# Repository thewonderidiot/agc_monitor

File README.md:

# AGC Monitor

This is a modern reimplementation of the AGC Monitor, for use with a real Apollo Guidance Computer. The panel layout and behavior were implemented according to pictures and descriptions from [E-2026, User's Guide to the AGC Monitor (Core Rope Simulator)](https://virtualagc.github.io/virtualagc/Documents/HSI-208487.pdf). Both the descriptions and pictures in this document leave a lot to be desired, so best guesses were made where concrete information was not available. All logic is implemented in a [Numato Lab Styx Z7 FPGA Module](https://numato.com/product/styx-zynq-7020-fpga-module), which is connected to the AGC via interface circuits powered by the AGC itself. Host interfacing is done via FTDI Synchronous FIFO. The host GUI is implemented in python using PySide2.

An early version of this project was shown in [episode 8 of the Apollo Guidance Computer Restoration video series](https://www.youtube.com/watch?v=ThOXgcOOA1M&list=PL-_93BVApb59FWrLZfdlisi_x7-Ut_-w7&index=11), and it played a central role for the rest of the restoration.

*Original AGC Monitor panel and modern GUI*

*Monitor board installed in an AGC for testing*

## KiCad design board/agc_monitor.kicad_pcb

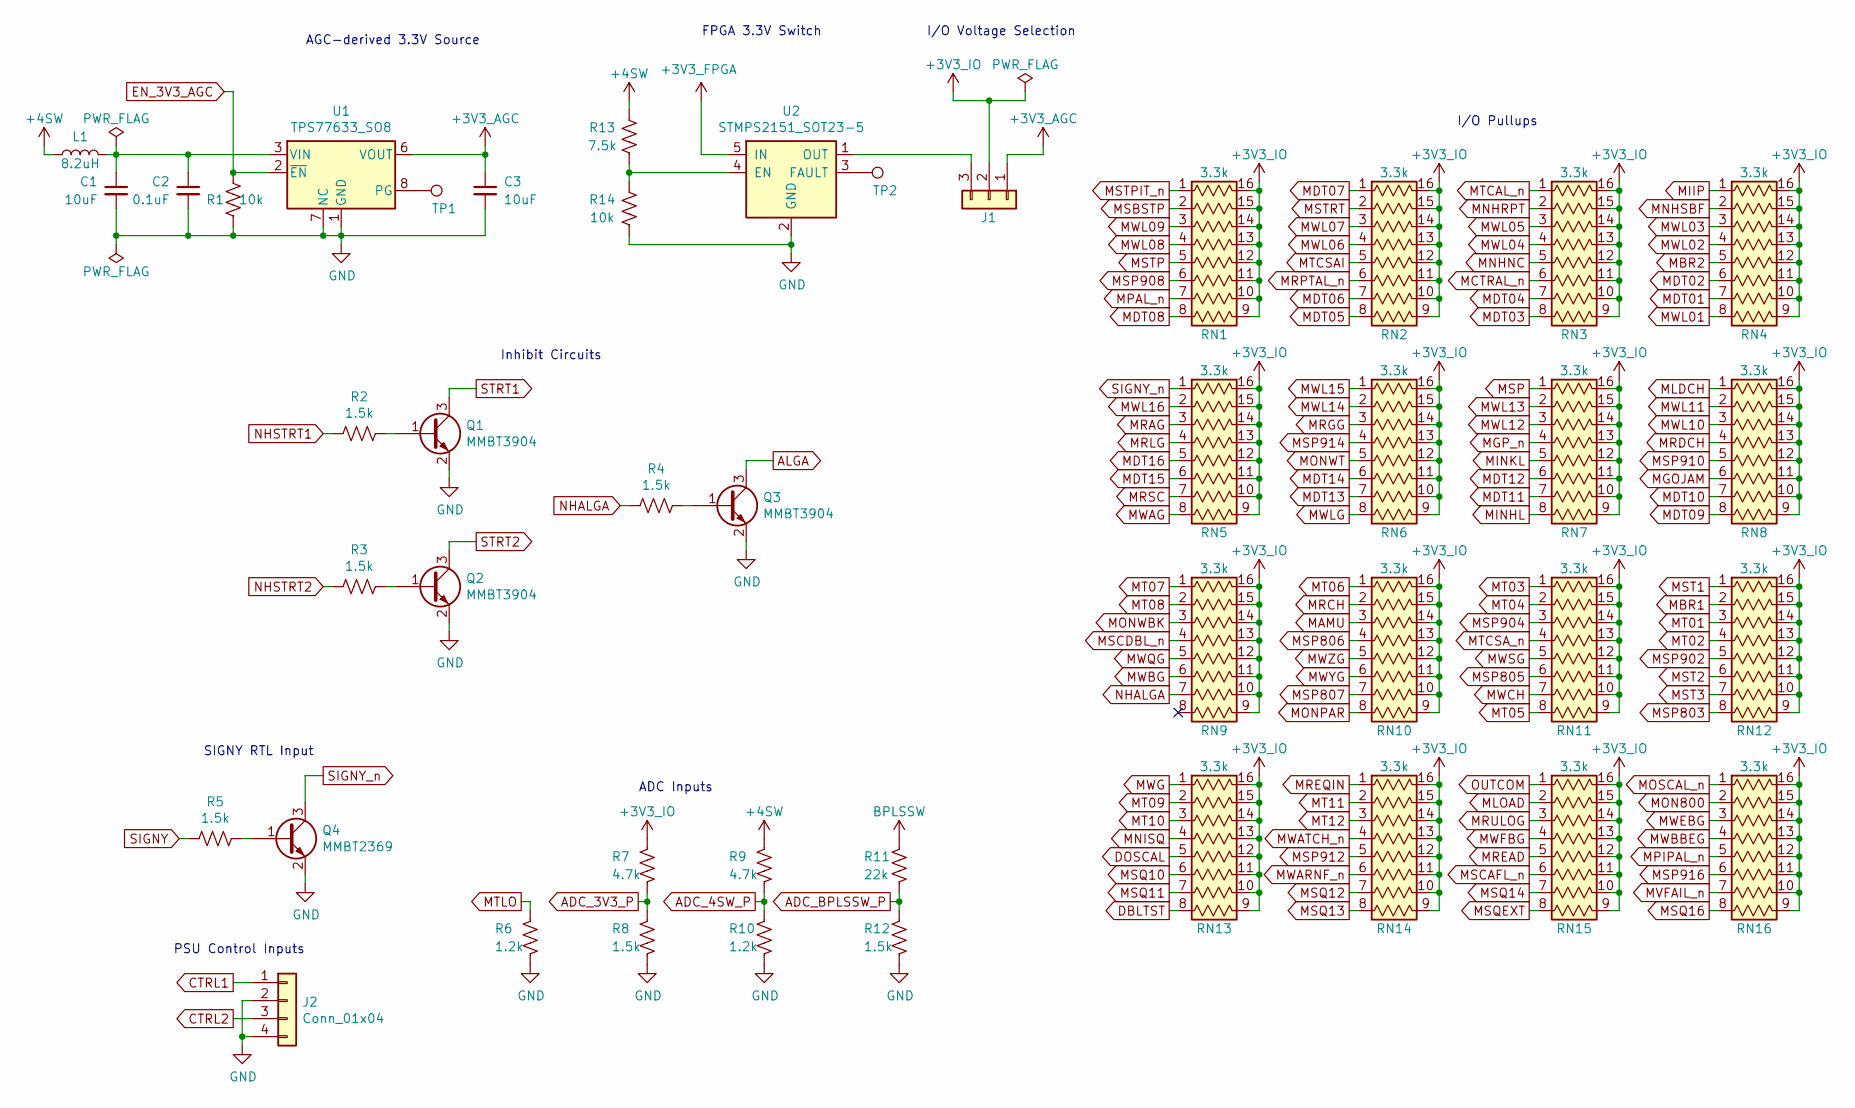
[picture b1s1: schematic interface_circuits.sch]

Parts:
C1, C3: 10uF; C_1206_3216Metric
C2: 0.1uF; C_0603_1608Metric
J1: Conn_01x03; PinHeader_1x03_P2.00mm_Vertical
J2: Conn_01x04; PinSocket_2x02_P2.54mm_Horizontal
L1: 8.2uH; L_1812_4532Metric
Q1, Q2, Q3: MMBT3904; SOT-23
Q4: MMBT2369; SOT-23
R1, R14: 10k; R_0603_1608Metric
R2, R3, R4, R5, R8, R12: 1.5k; R_0603_1608Metric
R6, R10: 1.2k; R_0603_1608Metric
R7, R9: 4.7k; R_0603_1608Metric
R11: 22k; R_0603_1608Metric
R13: 7.5k; R_0603_1608Metric
RN1, RN2, RN3, RN4, RN5, RN6, RN7, RN8, RN9, RN10, RN11, RN12, RN13, RN14, RN15, RN16: 3.3k; SOIC-16W_5.3x10.2mm_P1.27mm
TP1, TP2: TestPoint; TestPoint_Pad_D1.0mm
U1: TPS77633_SO8; SOIC-8_3.9x4.9mm_P1.27mm
U2: STMPS2151_SOT23-5; SOT-23-5

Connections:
+3V3_AGC: C3.1, J1.1, U1.5 (VOUT), U1.6 (VOUT)
+3V3_FPGA: U2.5 (IN); also elsewhere on the board
+3V3_IO: J1.2, R7.1, RN1.9 (R8B), RN1.10 (R7B), RN1.11 (R6B), RN1.12 (R5B), RN1.13 (R4B), RN1.14 (R3B), RN1.15 (R2B), RN1.16 (R1B), RN2.9 (R8B), RN2.10 (R7B), RN2.11 (R6B), RN2.12 (R5B), RN2.13 (R4B), RN2.14 (R3B), RN2.15 (R2B), RN2.16 (R1B), RN3.9 (R8B), RN3.10 (R7B), RN3.11 (R6B), RN3.12 (R5B), RN3.13 (R4B), RN3.14 (R3B), RN3.15 (R2B), RN3.16 (R1B), RN4.9 (R8B), RN4.10 (R7B), RN4.11 (R6B), RN4.12 (R5B), RN4.13 (R4B), RN4.14 (R3B), RN4.15 (R2B), RN4.16 (R1B), RN5.9 (R8B), RN5.10 (R7B), RN5.11 (R6B), RN5.12 (R5B), RN5.13 (R4B), RN5.14 (R3B), RN5.15 (R2B), RN5.16 (R1B), RN6.9 (R8B), RN6.10 (R7B), RN6.11 (R6B), RN6.12 (R5B), RN6.13 (R4B), RN6.14 (R3B), RN6.15 (R2B), RN6.16 (R1B), RN7.9 (R8B), RN7.10 (R7B), RN7.11 (R6B), RN7.12 (R5B), RN7.13 (R4B), RN7.14 (R3B), RN7.15 (R2B), RN7.16 (R1B), RN8.9 (R8B), RN8.10 (R7B), RN8.11 (R6B), RN8.12 (R5B), RN8.13 (R4B), RN8.14 (R3B), RN8.15 (R2B), RN8.16 (R1B), RN9.9 (R8B), RN9.10 (R7B), RN9.11 (R6B), RN9.12 (R5B), RN9.13 (R4B), RN9.14 (R3B), RN9.15 (R2B), RN9.16 (R1B), RN10.9 (R8B), RN10.10 (R7B), RN10.11 (R6B), RN10.12 (R5B), RN10.13 (R4B), RN10.14 (R3B), RN10.15 (R2B), RN10.16 (R1B), RN11.9 (R8B), RN11.10 (R7B), RN11.11 (R6B), RN11.12 (R5B), RN11.13 (R4B), RN11.14 (R3B), RN11.15 (R2B), RN11.16 (R1B), RN12.9 (R8B), RN12.10 (R7B), RN12.11 (R6B), RN12.12 (R5B), RN12.13 (R4B), RN12.14 (R3B), RN12.15 (R2B), RN12.16 (R1B), RN13.9 (R8B), RN13.10 (R7B), RN13.11 (R6B), RN13.12 (R5B), RN13.13 (R4B), RN13.14 (R3B), RN13.15 (R2B), RN13.16 (R1B), RN14.9 (R8B), RN14.10 (R7B), RN14.11 (R6B), RN14.12 (R5B), RN14.13 (R4B), RN14.14 (R3B), RN14.15 (R2B), RN14.16 (R1B), RN15.9 (R8B), RN15.10 (R7B), RN15.11 (R6B), RN15.12 (R5B), RN15.13 (R4B), RN15.14 (R3B), RN15.15 (R2B), RN15.16 (R1B), RN16.9 (R8B), RN16.10 (R7B), RN16.11 (R6B), RN16.12 (R5B), RN16.13 (R4B), RN16.14 (R3B), RN16.15 (R2B), RN16.16 (R1B); also elsewhere on the board
+4SW: L1.1, R9.1, R13.1; also elsewhere on the board
ADC_3V3_P: R7.2, R8.1; also elsewhere on the board
ADC_4SW_P: R9.2, R10.1; also elsewhere on the board
ADC_BPLSSW_P: R11.2, R12.1; also elsewhere on the board
ALGA: Q3.3 (C); also elsewhere on the board
BPLSSW: R11.1; also elsewhere on the board
CTRL1: J2.1; also elsewhere on the board
CTRL2: J2.3; also elsewhere on the board
DBLTST: RN13.8 (R8A); also elsewhere on the board
DOSCAL: RN13.5 (R5A); also elsewhere on the board
EN_3V3_AGC: R1.1, U1.2 (~EN~); also elsewhere on the board
GND: C1.2, C2.2, C3.2, J2.2, J2.4, Q1.2 (E), Q2.2 (E), Q3.2 (E), Q4.2 (E), R1.2, R6.2, R8.2, R10.2, R12.2, R14.2, U1.1 (GND), U1.7 (NC), U2.2 (GND); also elsewhere on the board
MAMU: RN10.3 (R3A); also elsewhere on the board
MBR1: RN12.2 (R2A); also elsewhere on the board
MBR2: RN4.5 (R5A); also elsewhere on the board
MCTRAL_n: RN3.6 (R6A); also elsewhere on the board
MDT01: RN4.7 (R7A); also elsewhere on the board
MDT02: RN4.6 (R6A); also elsewhere on the board
MDT03: RN3.8 (R8A); also elsewhere on the board
MDT04: RN3.7 (R7A); also elsewhere on the board
MDT05: RN2.8 (R8A); also elsewhere on the board
MDT06: RN2.7 (R7A); also elsewhere on the board
MDT07: RN2.1 (R1A); also elsewhere on the board
MDT08: RN1.8 (R8A); also elsewhere on the board
MDT09: RN8.8 (R8A); also elsewhere on the board
MDT10: RN8.7 (R7A); also elsewhere on the board
MDT11: RN7.7 (R7A); also elsewhere on the board
MDT12: RN7.6 (R6A); also elsewhere on the board
MDT13: RN6.7 (R7A); also elsewhere on the board
MDT14: RN6.6 (R6A); also elsewhere on the board
MDT15: RN5.6 (R6A); also elsewhere on the board
MDT16: RN5.5 (R5A); also elsewhere on the board
MGOJAM: RN8.6 (R6A); also elsewhere on the board
MGP_n: RN7.4 (R4A); also elsewhere on the board
MIIP: RN4.1 (R1A); also elsewhere on the board
MINHL: RN7.8 (R8A); also elsewhere on the board
MINKL: RN7.5 (R5A); also elsewhere on the board
MLDCH: RN8.1 (R1A); also elsewhere on the board
MLOAD: RN15.2 (R2A); also elsewhere on the board
MNHNC: RN3.5 (R5A); also elsewhere on the board
MNHRPT: RN3.2 (R2A); also elsewhere on the board
MNHSBF: RN4.2 (R2A); also elsewhere on the board
MNISQ: RN13.4 (R4A); also elsewhere on the board
MON800: RN16.2 (R2A); also elsewhere on the board
MONPAR: RN10.8 (R8A); also elsewhere on the board
MONWBK: RN9.3 (R3A); also elsewhere on the board
MONWT: RN6.5 (R5A); also elsewhere on the board
MOSCAL_n: RN16.1 (R1A); also elsewhere on the board
MPAL_n: RN1.7 (R7A); also elsewhere on the board
MPIPAL_n: RN16.5 (R5A); also elsewhere on the board
MRAG: RN5.3 (R3A); also elsewhere on the board
MRCH: RN10.2 (R2A); also elsewhere on the board
MRDCH: RN8.4 (R4A); also elsewhere on the board
MREAD: RN15.5 (R5A); also elsewhere on the board
MREQIN: RN14.1 (R1A); also elsewhere on the board
MRGG: RN6.3 (R3A); also elsewhere on the board
MRLG: RN5.4 (R4A); also elsewhere on the board
MRPTAL_n: RN2.6 (R6A); also elsewhere on the board
MRSC: RN5.7 (R7A); also elsewhere on the board
MRULOG: RN15.3 (R3A); also elsewhere on the board
MSBSTP: RN1.2 (R2A); also elsewhere on the board
MSCAFL_n: RN15.6 (R6A); also elsewhere on the board
MSCDBL_n: RN9.4 (R4A); also elsewhere on the board
MSP: RN7.1 (R1A); also elsewhere on the board
MSP803: RN12.8 (R8A); also elsewhere on the board
MSP805: RN11.6 (R6A); also elsewhere on the board
MSP806: RN10.4 (R4A); also elsewhere on the board
MSP807: RN10.7 (R7A); also elsewhere on the board
MSP902: RN12.5 (R5A); also elsewhere on the board
MSP904: RN11.3 (R3A); also elsewhere on the board
MSP908: RN1.6 (R6A); also elsewhere on the board
MSP910: RN8.5 (R5A); also elsewhere on the board
MSP912: RN14.5 (R5A); also elsewhere on the board
MSP914: RN6.4 (R4A); also elsewhere on the board
MSP916: RN16.6 (R6A); also elsewhere on the board
MSQ10: RN13.6 (R6A); also elsewhere on the board
MSQ11: RN13.7 (R7A); also elsewhere on the board
MSQ12: RN14.7 (R7A); also elsewhere on the board
MSQ13: RN14.8 (R8A); also elsewhere on the board
MSQ14: RN15.7 (R7A); also elsewhere on the board
MSQ16: RN16.8 (R8A); also elsewhere on the board
MSQEXT: RN15.8 (R8A); also elsewhere on the board
MST1: RN12.1 (R1A); also elsewhere on the board
MST2: RN12.6 (R6A); also elsewhere on the board
MST3: RN12.7 (R7A); also elsewhere on the board
MSTP: RN1.5 (R5A); also elsewhere on the board
MSTPIT_n: RN1.1 (R1A); also elsewhere on the board
MSTRT: RN2.2 (R2A); also elsewhere on the board
MT01: RN12.3 (R3A); also elsewhere on the board
MT02: RN12.4 (R4A); also elsewhere on the board
MT03: RN11.1 (R1A); also elsewhere on the board
MT04: RN11.2 (R2A); also elsewhere on the board
MT05: RN11.8 (R8A); also elsewhere on the board
MT06: RN10.1 (R1A); also elsewhere on the board
MT07: RN9.1 (R1A); also elsewhere on the board
MT08: RN9.2 (R2A); also elsewhere on the board
MT09: RN13.2 (R2A); also elsewhere on the board
MT10: RN13.3 (R3A); also elsewhere on the board
MT11: RN14.2 (R2A); also elsewhere on the board
MT12: RN14.3 (R3A); also elsewhere on the board
MTCAL_n: RN3.1 (R1A); also elsewhere on the board
MTCSAI: RN2.5 (R5A); also elsewhere on the board
MTCSA_n: RN11.4 (R4A); also elsewhere on the board
MTLO: R6.1; also elsewhere on the board
MVFAIL_n: RN16.7 (R7A); also elsewhere on the board
MWAG: RN5.8 (R8A); also elsewhere on the board
MWARNF_n: RN14.6 (R6A); also elsewhere on the board
MWATCH_n: RN14.4 (R4A); also elsewhere on the board
MWBBEG: RN16.4 (R4A); also elsewhere on the board
MWBG: RN9.6 (R6A); also elsewhere on the board
MWCH: RN11.7 (R7A); also elsewhere on the board
MWEBG: RN16.3 (R3A); also elsewhere on the board
MWFBG: RN15.4 (R4A); also elsewhere on the board
MWG: RN13.1 (R1A); also elsewhere on the board
MWL01: RN4.8 (R8A); also elsewhere on the board
MWL02: RN4.4 (R4A); also elsewhere on the board
MWL03: RN4.3 (R3A); also elsewhere on the board
MWL04: RN3.4 (R4A); also elsewhere on the board
MWL05: RN3.3 (R3A); also elsewhere on the board
MWL06: RN2.4 (R4A); also elsewhere on the board
MWL07: RN2.3 (R3A); also elsewhere on the board
MWL08: RN1.4 (R4A); also elsewhere on the board
MWL09: RN1.3 (R3A); also elsewhere on the board
MWL10: RN8.3 (R3A); also elsewhere on the board
MWL11: RN8.2 (R2A); also elsewhere on the board
MWL12: RN7.3 (R3A); also elsewhere on the board
MWL13: RN7.2 (R2A); also elsewhere on the board
MWL14: RN6.2 (R2A); also elsewhere on the board
MWL15: RN6.1 (R1A); also elsewhere on the board
MWL16: RN5.2 (R2A); also elsewhere on the board
MWLG: RN6.8 (R8A); also elsewhere on the board
MWQG: RN9.5 (R5A); also elsewhere on the board
MWSG: RN11.5 (R5A); also elsewhere on the board
MWYG: RN10.6 (R6A); also elsewhere on the board
MWZG: RN10.5 (R5A); also elsewhere on the board
NHALGA: R4.2, RN9.7 (R7A); also elsewhere on the board
NHSTRT1: R2.2; also elsewhere on the board
NHSTRT2: R3.2; also elsewhere on the board
unnamed: C1.1, C2.1, L1.2, U1.3 (VIN), U1.4 (VIN)
unnamed: J1.3, U2.1 (OUT)
unnamed: Q1.1 (B), R2.1
unnamed: Q2.1 (B), R3.1
unnamed: Q3.1 (B), R4.1
unnamed: Q4.1 (B), R5.1
unnamed: R13.2, R14.1, U2.4 (EN)
unnamed: TP1.1, U1.8 (PG)
unnamed: TP2.1, U2.3 (FAULT)
OUTCOM: RN15.1 (R1A); also elsewhere on the board
SIGNY: R5.2; also elsewhere on the board
SIGNY_n: Q4.3 (C), RN5.1 (R1A); also elsewhere on the board
STRT1: Q1.3 (C); also elsewhere on the board
STRT2: Q2.3 (C); also elsewhere on the board

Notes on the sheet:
AGC-derived 3.3V Source
I/O Voltage Selection
ADC Inputs
I/O Pullups
Inhibit Circuits
PSU Control Inputs
SIGNY RTL Input
FPGA 3.3V Switch

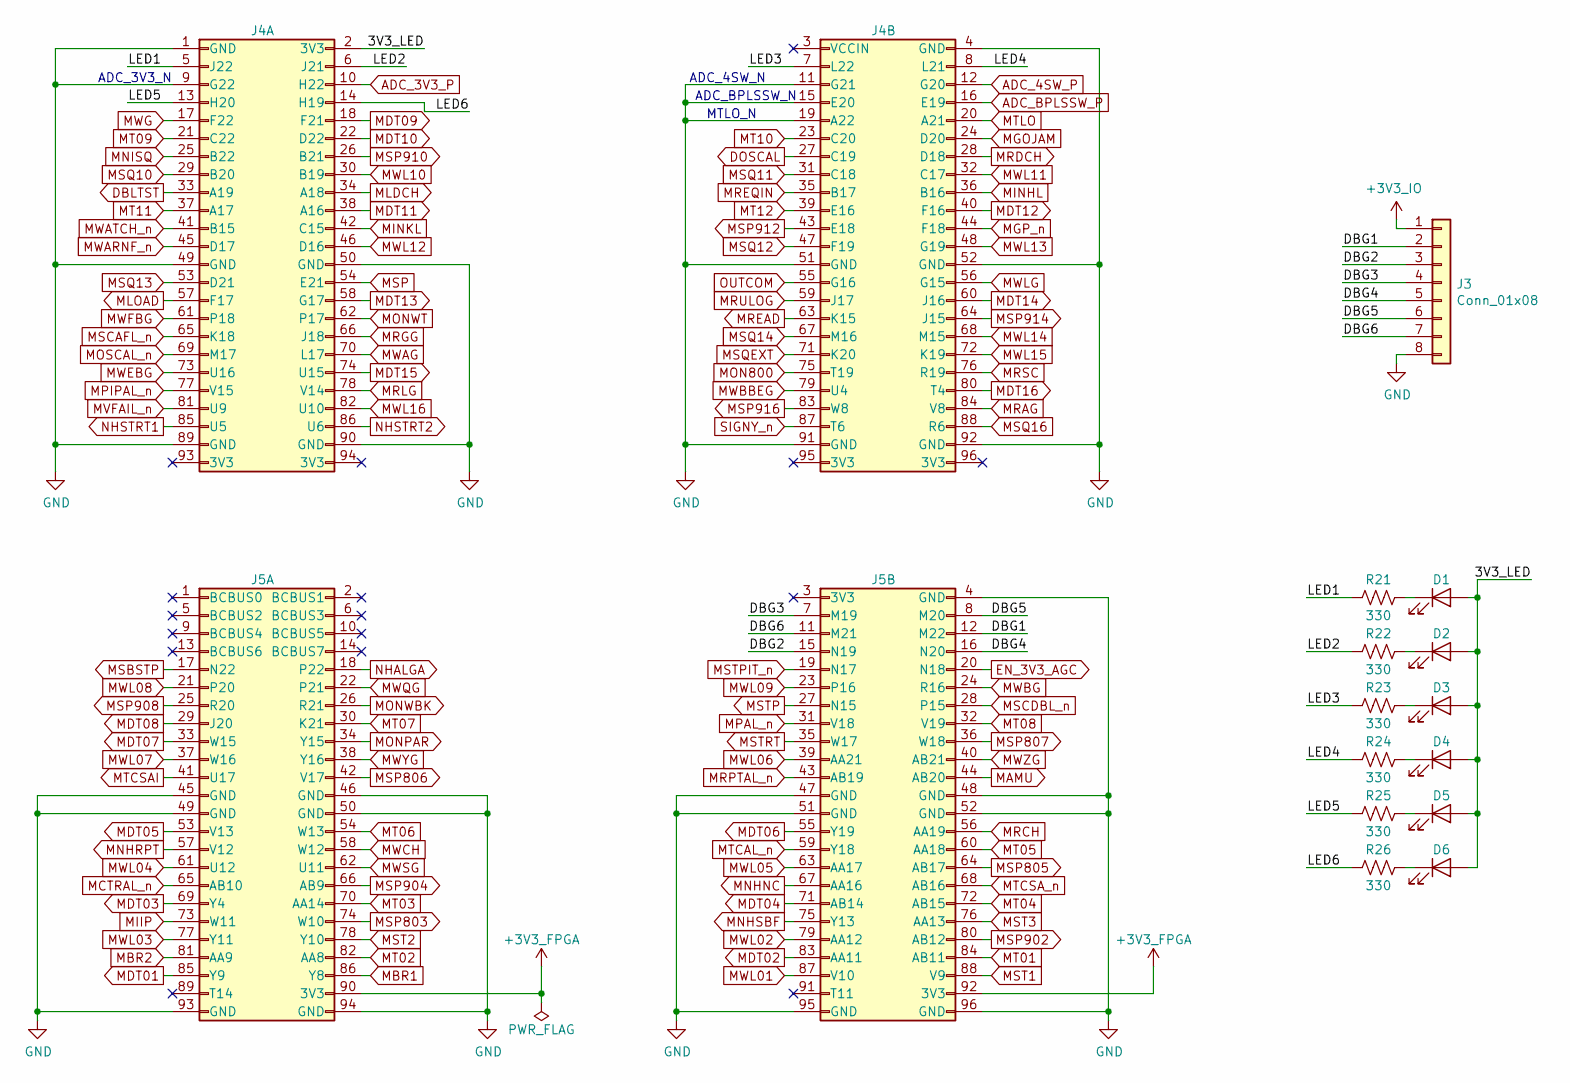
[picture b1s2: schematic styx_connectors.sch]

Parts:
D1, D2, D3, D4, D5, D6: LED; LED_0603_1608Metric
J3: Conn_01x08; PinSocket_2x04_P2.54mm_Horizontal
J4: Styx_P4; PinHeader_4x24_P2.54mm_Vertical
J5: Styx_P5; PinHeader_4x24_P2.54mm_Vertical
R21, R22, R23, R24, R25, R26: 330; R_0603_1608Metric

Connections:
+3V3_FPGA: J5.90 (3V3), J5.92 (3V3); also elsewhere on the board
+3V3_IO: J3.1; also elsewhere on the board
/StyxConnectors/3V3_LED: D1.2 (A), D2.2 (A), D3.2 (A), D4.2 (A), D5.2 (A), D6.2 (A), J4.2 (3V3)
/StyxConnectors/DBG1: J3.2, J5.12 (M22)
/StyxConnectors/DBG2: J3.3, J5.15 (N19)
/StyxConnectors/DBG3: J3.4, J5.7 (M19)
/StyxConnectors/DBG4: J3.5, J5.16 (N20)
/StyxConnectors/DBG5: J3.6, J5.8 (M20)
/StyxConnectors/DBG6: J3.7, J5.11 (M21)
/StyxConnectors/LED1: J4.5 (J22), R21.2
/StyxConnectors/LED2: J4.6 (J21), R22.2
/StyxConnectors/LED3: J4.7 (L22), R23.2
/StyxConnectors/LED4: J4.8 (L21), R24.2
/StyxConnectors/LED5: J4.13 (H20), R25.2
/StyxConnectors/LED6: J4.14 (H19), R26.2
ADC_3V3_P: J4.10 (H22); also elsewhere on the board
ADC_4SW_P: J4.12 (G20); also elsewhere on the board
ADC_BPLSSW_P: J4.16 (E19); also elsewhere on the board
DBLTST: J4.33 (A19); also elsewhere on the board
DOSCAL: J4.27 (C19); also elsewhere on the board
EN_3V3_AGC: J5.20 (N18); also elsewhere on the board
GND: J3.8, J4.1 (GND), J4.4 (GND), J4.9 (G22), J4.11 (G21), J4.15 (E20), J4.19 (A22), J4.49 (GND), J4.50 (GND), J4.51 (GND), J4.52 (GND), J4.89 (GND), J4.90 (GND), J4.91 (GND), J4.92 (GND), J5.4 (GND), J5.45 (GND), J5.46 (GND), J5.47 (GND), J5.48 (GND), J5.49 (GND), J5.50 (GND), J5.51 (GND), J5.52 (GND), J5.93 (GND), J5.94 (GND), J5.95 (GND), J5.96 (GND); also elsewhere on the board
MAMU: J5.44 (AB20); also elsewhere on the board
MBR1: J5.86 (Y8); also elsewhere on the board
MBR2: J5.81 (AA9); also elsewhere on the board
MCTRAL_n: J5.65 (AB10); also elsewhere on the board
MDT01: J5.85 (Y9); also elsewhere on the board
MDT02: J5.83 (AA11); also elsewhere on the board
MDT03: J5.69 (Y4); also elsewhere on the board
MDT04: J5.71 (AB14); also elsewhere on the board
MDT05: J5.53 (V13); also elsewhere on the board
MDT06: J5.55 (Y19); also elsewhere on the board
MDT07: J5.33 (W15); also elsewhere on the board
MDT08: J5.29 (J20); also elsewhere on the board
MDT09: J4.18 (F21); also elsewhere on the board
MDT10: J4.22 (D22); also elsewhere on the board
MDT11: J4.38 (A16); also elsewhere on the board
MDT12: J4.40 (F16); also elsewhere on the board
MDT13: J4.58 (G17); also elsewhere on the board
MDT14: J4.60 (J16); also elsewhere on the board
MDT15: J4.74 (U15); also elsewhere on the board
MDT16: J4.80 (T4); also elsewhere on the board
MGOJAM: J4.24 (D20); also elsewhere on the board
MGP_n: J4.44 (F18); also elsewhere on the board
MIIP: J5.73 (W11); also elsewhere on the board
MINHL: J4.36 (B16); also elsewhere on the board
MINKL: J4.42 (C15); also elsewhere on the board
MLDCH: J4.34 (A18); also elsewhere on the board
MLOAD: J4.57 (F17); also elsewhere on the board
MNHNC: J5.67 (AA16); also elsewhere on the board
MNHRPT: J5.57 (V12); also elsewhere on the board
MNHSBF: J5.75 (Y13); also elsewhere on the board
MNISQ: J4.25 (B22); also elsewhere on the board
MON800: J4.75 (T19); also elsewhere on the board
MONPAR: J5.34 (Y15); also elsewhere on the board
MONWBK: J5.26 (R21); also elsewhere on the board
MONWT: J4.62 (P17); also elsewhere on the board
MOSCAL_n: J4.69 (M17); also elsewhere on the board
MPAL_n: J5.31 (V18); also elsewhere on the board
MPIPAL_n: J4.77 (V15); also elsewhere on the board
MRAG: J4.84 (V8); also elsewhere on the board
MRCH: J5.56 (AA19); also elsewhere on the board
MRDCH: J4.28 (D18); also elsewhere on the board
MREAD: J4.63 (K15); also elsewhere on the board
MREQIN: J4.35 (B17); also elsewhere on the board
MRGG: J4.66 (J18); also elsewhere on the board
MRLG: J4.78 (V14); also elsewhere on the board
MRPTAL_n: J5.43 (AB19); also elsewhere on the board
MRSC: J4.76 (R19); also elsewhere on the board
MRULOG: J4.59 (J17); also elsewhere on the board
MSBSTP: J5.17 (N22); also elsewhere on the board
MSCAFL_n: J4.65 (K18); also elsewhere on the board
MSCDBL_n: J5.28 (P15); also elsewhere on the board
MSP: J4.54 (E21); also elsewhere on the board
MSP803: J5.74 (W10); also elsewhere on the board
MSP805: J5.64 (AB17); also elsewhere on the board
MSP806: J5.42 (V17); also elsewhere on the board
MSP807: J5.36 (W18); also elsewhere on the board
MSP902: J5.80 (AB12); also elsewhere on the board
MSP904: J5.66 (AB9); also elsewhere on the board
MSP908: J5.25 (R20); also elsewhere on the board
MSP910: J4.26 (B21); also elsewhere on the board
MSP912: J4.43 (E18); also elsewhere on the board
MSP914: J4.64 (J15); also elsewhere on the board
MSP916: J4.83 (W8); also elsewhere on the board
MSQ10: J4.29 (B20); also elsewhere on the board
MSQ11: J4.31 (C18); also elsewhere on the board
MSQ12: J4.47 (F19); also elsewhere on the board
MSQ13: J4.53 (D21); also elsewhere on the board
MSQ14: J4.67 (M16); also elsewhere on the board
MSQ16: J4.88 (R6); also elsewhere on the board
MSQEXT: J4.71 (K20); also elsewhere on the board
MST1: J5.88 (V9); also elsewhere on the board
MST2: J5.78 (Y10); also elsewhere on the board
MST3: J5.76 (AA13); also elsewhere on the board
MSTP: J5.27 (N15); also elsewhere on the board
MSTPIT_n: J5.19 (N17); also elsewhere on the board
MSTRT: J5.35 (W17); also elsewhere on the board
MT01: J5.84 (AB11); also elsewhere on the board
MT02: J5.82 (AA8); also elsewhere on the board
MT03: J5.70 (AA14); also elsewhere on the board
MT04: J5.72 (AB15); also elsewhere on the board
MT05: J5.60 (AA18); also elsewhere on the board
MT06: J5.54 (W13); also elsewhere on the board
MT07: J5.30 (K21); also elsewhere on the board
MT08: J5.32 (V19); also elsewhere on the board
MT09: J4.21 (C22); also elsewhere on the board
MT10: J4.23 (C20); also elsewhere on the board
MT11: J4.37 (A17); also elsewhere on the board
MT12: J4.39 (E16); also elsewhere on the board
MTCAL_n: J5.59 (Y18); also elsewhere on the board
MTCSAI: J5.41 (U17); also elsewhere on the board
MTCSA_n: J5.68 (AB16); also elsewhere on the board
MTLO: J4.20 (A21); also elsewhere on the board
MVFAIL_n: J4.81 (U9); also elsewhere on the board
MWAG: J4.70 (L17); also elsewhere on the board
MWARNF_n: J4.45 (D17); also elsewhere on the board
MWATCH_n: J4.41 (B15); also elsewhere on the board
MWBBEG: J4.79 (U4); also elsewhere on the board
MWBG: J5.24 (R16); also elsewhere on the board
MWCH: J5.58 (W12); also elsewhere on the board
MWEBG: J4.73 (U16); also elsewhere on the board
MWFBG: J4.61 (P18); also elsewhere on the board
MWG: J4.17 (F22); also elsewhere on the board
MWL01: J5.87 (V10); also elsewhere on the board
MWL02: J5.79 (AA12); also elsewhere on the board
MWL03: J5.77 (Y11); also elsewhere on the board
MWL04: J5.61 (U12); also elsewhere on the board
MWL05: J5.63 (AA17); also elsewhere on the board
MWL06: J5.39 (AA21); also elsewhere on the board
MWL07: J5.37 (W16); also elsewhere on the board
MWL08: J5.21 (P20); also elsewhere on the board
MWL09: J5.23 (P16); also elsewhere on the board
MWL10: J4.30 (B19); also elsewhere on the board
MWL11: J4.32 (C17); also elsewhere on the board
MWL12: J4.46 (D16); also elsewhere on the board
MWL13: J4.48 (G19); also elsewhere on the board
MWL14: J4.68 (M15); also elsewhere on the board
MWL15: J4.72 (K19); also elsewhere on the board
MWL16: J4.82 (U10); also elsewhere on the board
MWLG: J4.56 (G15); also elsewhere on the board
MWQG: J5.22 (P21); also elsewhere on the board
MWSG: J5.62 (U11); also elsewhere on the board
MWYG: J5.38 (Y16); also elsewhere on the board
MWZG: J5.40 (AB21); also elsewhere on the board
NHALGA: J5.18 (P22); also elsewhere on the board
NHSTRT1: J4.85 (U5); also elsewhere on the board
NHSTRT2: J4.86 (U6); also elsewhere on the board
unnamed: D1.1 (K), R21.1
unnamed: D2.1 (K), R22.1
unnamed: D3.1 (K), R23.1
unnamed: D4.1 (K), R24.1
unnamed: D5.1 (K), R25.1
unnamed: D6.1 (K), R26.1
OUTCOM: J4.55 (G16); also elsewhere on the board
SIGNY_n: J4.87 (T6); also elsewhere on the board

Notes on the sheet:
ADC_BPLSSW_N
ADC_4SW_N
MTLO_N
ADC_3V3_N

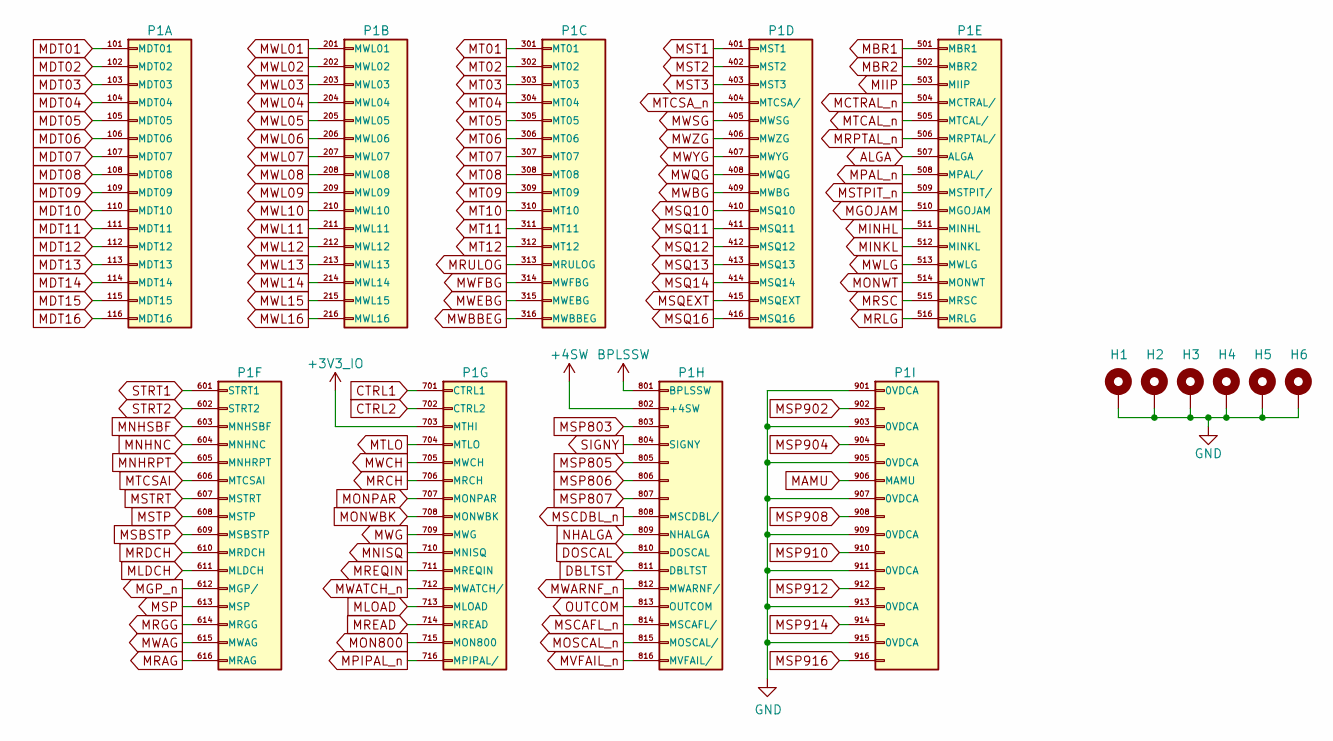
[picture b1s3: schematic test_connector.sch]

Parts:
H1, H2, H3, H4, H5, H6: MountingHole_Pad; MountingHole_ANSI_4
P1: test_connector

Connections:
+3V3_IO: P1.703 (MTHI); also elsewhere on the board
+4SW: P1.802 (+4SW); also elsewhere on the board
ALGA: P1.507 (ALGA); also elsewhere on the board
BPLSSW: P1.801 (BPLSSW); also elsewhere on the board
CTRL1: P1.701 (CTRL1); also elsewhere on the board
CTRL2: P1.702 (CTRL2); also elsewhere on the board
DBLTST: P1.811 (DBLTST); also elsewhere on the board
DOSCAL: P1.810 (DOSCAL); also elsewhere on the board
GND: H1.1, H2.1, H3.1, H4.1, H5.1, H6.1, P1.901 (0VDCA), P1.903 (0VDCA), P1.905 (0VDCA), P1.907 (0VDCA), P1.909 (0VDCA), P1.911 (0VDCA), P1.913 (0VDCA), P1.915 (0VDCA); also elsewhere on the board
MAMU: P1.906 (MAMU); also elsewhere on the board
MBR1: P1.501 (MBR1); also elsewhere on the board
MBR2: P1.502 (MBR2); also elsewhere on the board
MCTRAL_n: P1.504 (MCTRAL/); also elsewhere on the board
MDT01: P1.101 (MDT01); also elsewhere on the board
MDT02: P1.102 (MDT02); also elsewhere on the board
MDT03: P1.103 (MDT03); also elsewhere on the board
MDT04: P1.104 (MDT04); also elsewhere on the board
MDT05: P1.105 (MDT05); also elsewhere on the board
MDT06: P1.106 (MDT06); also elsewhere on the board
MDT07: P1.107 (MDT07); also elsewhere on the board
MDT08: P1.108 (MDT08); also elsewhere on the board
MDT09: P1.109 (MDT09); also elsewhere on the board
MDT10: P1.110 (MDT10); also elsewhere on the board
MDT11: P1.111 (MDT11); also elsewhere on the board
MDT12: P1.112 (MDT12); also elsewhere on the board
MDT13: P1.113 (MDT13); also elsewhere on the board
MDT14: P1.114 (MDT14); also elsewhere on the board
MDT15: P1.115 (MDT15); also elsewhere on the board
MDT16: P1.116 (MDT16); also elsewhere on the board
MGOJAM: P1.510 (MGOJAM); also elsewhere on the board
MGP_n: P1.612 (MGP/); also elsewhere on the board
MIIP: P1.503 (MIIP); also elsewhere on the board
MINHL: P1.511 (MINHL); also elsewhere on the board
MINKL: P1.512 (MINKL); also elsewhere on the board
MLDCH: P1.611 (MLDCH); also elsewhere on the board
MLOAD: P1.713 (MLOAD); also elsewhere on the board
MNHNC: P1.604 (MNHNC); also elsewhere on the board
MNHRPT: P1.605 (MNHRPT); also elsewhere on the board
MNHSBF: P1.603 (MNHSBF); also elsewhere on the board
MNISQ: P1.710 (MNISQ); also elsewhere on the board
MON800: P1.715 (MON800); also elsewhere on the board
MONPAR: P1.707 (MONPAR); also elsewhere on the board
MONWBK: P1.708 (MONWBK); also elsewhere on the board
MONWT: P1.514 (MONWT); also elsewhere on the board
MOSCAL_n: P1.815 (MOSCAL/); also elsewhere on the board
MPAL_n: P1.508 (MPAL/); also elsewhere on the board
MPIPAL_n: P1.716 (MPIPAL/); also elsewhere on the board
MRAG: P1.616 (MRAG); also elsewhere on the board
MRCH: P1.706 (MRCH); also elsewhere on the board
MRDCH: P1.610 (MRDCH); also elsewhere on the board
MREAD: P1.714 (MREAD); also elsewhere on the board
MREQIN: P1.711 (MREQIN); also elsewhere on the board
MRGG: P1.614 (MRGG); also elsewhere on the board
MRLG: P1.516 (MRLG); also elsewhere on the board
MRPTAL_n: P1.506 (MRPTAL/); also elsewhere on the board
MRSC: P1.515 (MRSC); also elsewhere on the board
MRULOG: P1.313 (MRULOG); also elsewhere on the board
MSBSTP: P1.609 (MSBSTP); also elsewhere on the board
MSCAFL_n: P1.814 (MSCAFL/); also elsewhere on the board
MSCDBL_n: P1.808 (MSCDBL/); also elsewhere on the board
MSP: P1.613 (MSP); also elsewhere on the board
MSP803: P1.803; also elsewhere on the board
MSP805: P1.805; also elsewhere on the board
MSP806: P1.806; also elsewhere on the board
MSP807: P1.807; also elsewhere on the board
MSP902: P1.902; also elsewhere on the board
MSP904: P1.904; also elsewhere on the board
MSP908: P1.908; also elsewhere on the board
MSP910: P1.910; also elsewhere on the board
MSP912: P1.912; also elsewhere on the board
MSP914: P1.914; also elsewhere on the board
MSP916: P1.916; also elsewhere on the board
MSQ10: P1.410 (MSQ10); also elsewhere on the board
MSQ11: P1.411 (MSQ11); also elsewhere on the board
MSQ12: P1.412 (MSQ12); also elsewhere on the board
MSQ13: P1.413 (MSQ13); also elsewhere on the board
MSQ14: P1.414 (MSQ14); also elsewhere on the board
MSQ16: P1.416 (MSQ16); also elsewhere on the board
MSQEXT: P1.415 (MSQEXT); also elsewhere on the board
MST1: P1.401 (MST1); also elsewhere on the board
MST2: P1.402 (MST2); also elsewhere on the board
MST3: P1.403 (MST3); also elsewhere on the board
MSTP: P1.608 (MSTP); also elsewhere on the board
MSTPIT_n: P1.509 (MSTPIT/); also elsewhere on the board
MSTRT: P1.607 (MSTRT); also elsewhere on the board
MT01: P1.301 (MT01); also elsewhere on the board
MT02: P1.302 (MT02); also elsewhere on the board
MT03: P1.303 (MT03); also elsewhere on the board
MT04: P1.304 (MT04); also elsewhere on the board
MT05: P1.305 (MT05); also elsewhere on the board
MT06: P1.306 (MT06); also elsewhere on the board
MT07: P1.307 (MT07); also elsewhere on the board
MT08: P1.308 (MT08); also elsewhere on the board
MT09: P1.309 (MT09); also elsewhere on the board
MT10: P1.310 (MT10); also elsewhere on the board
MT11: P1.311 (MT11); also elsewhere on the board
MT12: P1.312 (MT12); also elsewhere on the board
MTCAL_n: P1.505 (MTCAL/); also elsewhere on the board
MTCSAI: P1.606 (MTCSAI); also elsewhere on the board
MTCSA_n: P1.404 (MTCSA/); also elsewhere on the board
MTLO: P1.704 (MTLO); also elsewhere on the board
MVFAIL_n: P1.816 (MVFAIL/); also elsewhere on the board
MWAG: P1.615 (MWAG); also elsewhere on the board
MWARNF_n: P1.812 (MWARNF/); also elsewhere on the board
MWATCH_n: P1.712 (MWATCH/); also elsewhere on the board
MWBBEG: P1.316 (MWBBEG); also elsewhere on the board
MWBG: P1.409 (MWBG); also elsewhere on the board
MWCH: P1.705 (MWCH); also elsewhere on the board
MWEBG: P1.315 (MWEBG); also elsewhere on the board
MWFBG: P1.314 (MWFBG); also elsewhere on the board
MWG: P1.709 (MWG); also elsewhere on the board
MWL01: P1.201 (MWL01); also elsewhere on the board
MWL02: P1.202 (MWL02); also elsewhere on the board
MWL03: P1.203 (MWL03); also elsewhere on the board
MWL04: P1.204 (MWL04); also elsewhere on the board
MWL05: P1.205 (MWL05); also elsewhere on the board
MWL06: P1.206 (MWL06); also elsewhere on the board
MWL07: P1.207 (MWL07); also elsewhere on the board
MWL08: P1.208 (MWL08); also elsewhere on the board
MWL09: P1.209 (MWL09); also elsewhere on the board
MWL10: P1.210 (MWL10); also elsewhere on the board
MWL11: P1.211 (MWL11); also elsewhere on the board
MWL12: P1.212 (MWL12); also elsewhere on the board
MWL13: P1.213 (MWL13); also elsewhere on the board
MWL14: P1.214 (MWL14); also elsewhere on the board
MWL15: P1.215 (MWL15); also elsewhere on the board
MWL16: P1.216 (MWL16); also elsewhere on the board
MWLG: P1.513 (MWLG); also elsewhere on the board
MWQG: P1.408 (MWQG); also elsewhere on the board
MWSG: P1.405 (MWSG); also elsewhere on the board
MWYG: P1.407 (MWYG); also elsewhere on the board
MWZG: P1.406 (MWZG); also elsewhere on the board
NHALGA: P1.809 (NHALGA); also elsewhere on the board
OUTCOM: P1.813 (OUTCOM); also elsewhere on the board
SIGNY: P1.804 (SIGNY); also elsewhere on the board
STRT1: P1.601 (STRT1); also elsewhere on the board
STRT2: P1.602 (STRT2); also elsewhere on the board

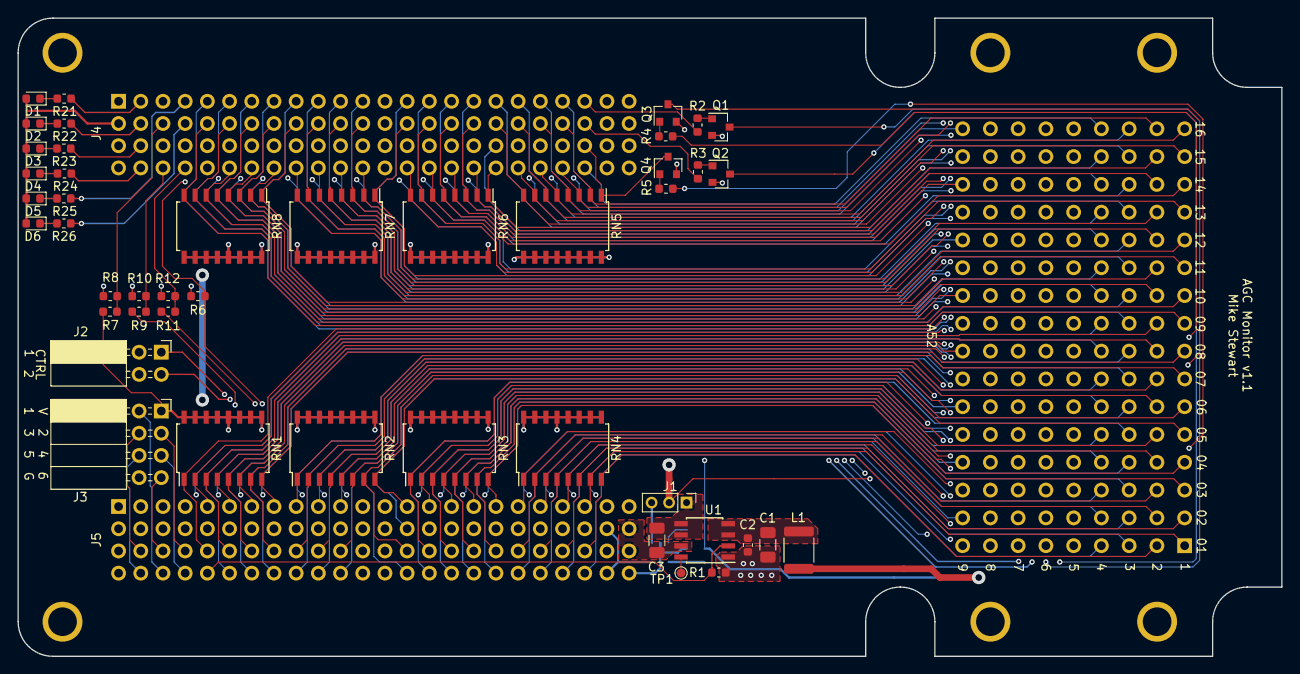
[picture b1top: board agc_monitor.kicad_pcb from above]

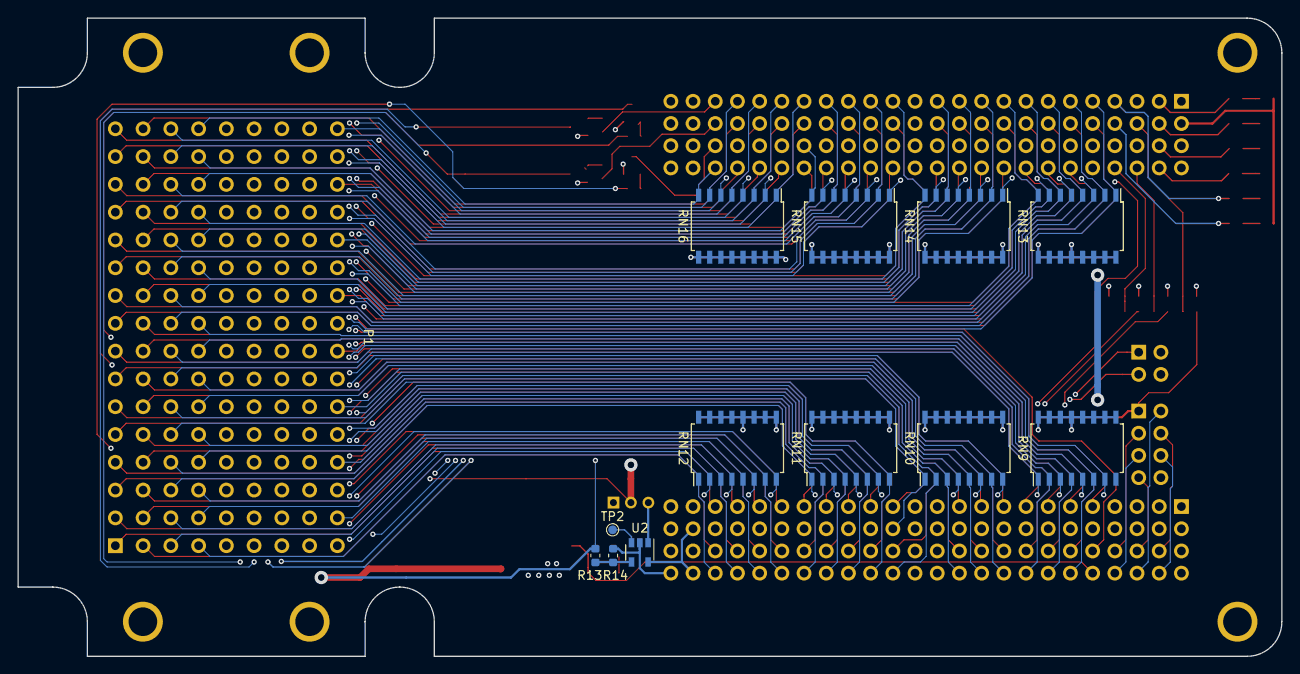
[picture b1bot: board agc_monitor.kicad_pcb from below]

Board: 4 copper layers, 144.6 x 73.0 mm, 66 parts (14 on the bottom side), 174 nets.
